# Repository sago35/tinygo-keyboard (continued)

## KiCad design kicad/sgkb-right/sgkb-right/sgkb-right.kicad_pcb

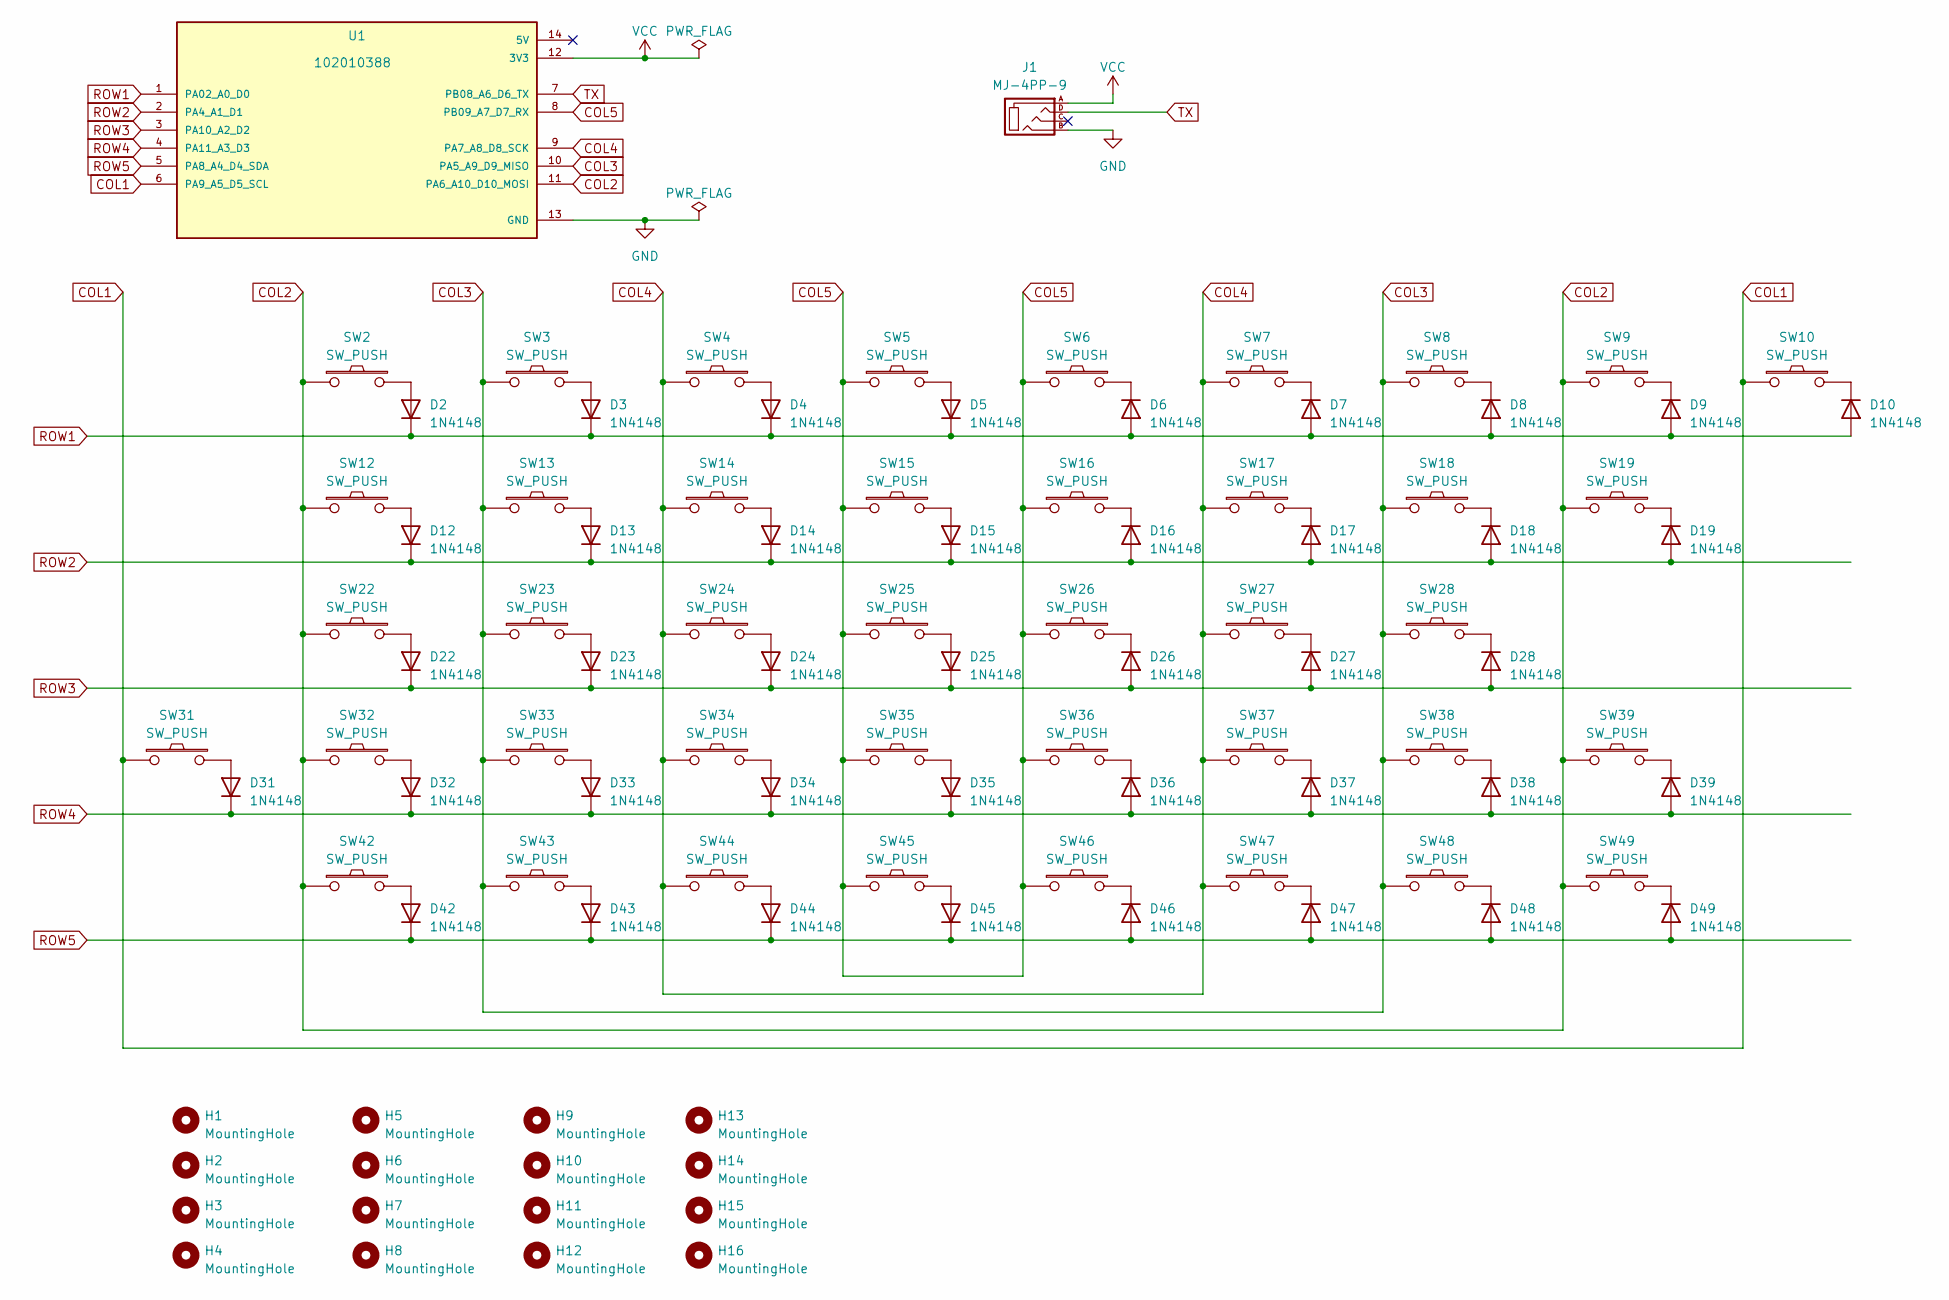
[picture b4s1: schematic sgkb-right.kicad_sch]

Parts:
D2, D3, D4, D5, D6, D7, D8, D9, D10, D12, D13, D14, D15, D16, D17, D18, D19, D22, D23, D24, D25, D26, D27, D28, D31, D32, D33, D34, D35, D36, D37, D38, D39, D42, D43, D44, D45, D46, D47, D48, D49: 1N4148; D3_SMD_v2
H1, H2, H3, H4, H5, H6, H7, H8, H9, H10, H11, H12, H13, H14, H15, H16: MountingHole; MountingHole_2.2mm_M2
J1: MJ-4PP-9; MJ-4PP-9_1side
SW2, SW3, SW4, SW5, SW6, SW7, SW8, SW9, SW10, SW12, SW13, SW14, SW15, SW16, SW17, SW18, SW22, SW23, SW24, SW25, SW26, SW27, SW28, SW31, SW32, SW33, SW34, SW35, SW36, SW37, SW38, SW39, SW42, SW43, SW44, SW45, SW46, SW47, SW48, SW49: SW_PUSH; CherryMX_Hotswap
SW19: SW_PUSH; CherryMX_Hotswap_with_2u_stabilizer
U1: 102010388; xiao; PARTREV N/A

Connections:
COL1: SW10.1, SW31.1, U1.6 (PA9_A5_D5_SCL)
COL2: SW2.1, SW9.1, SW12.1, SW19.1, SW22.1, SW32.1, SW39.1, SW42.1, SW49.1, U1.11 (PA6_A10_D10_MOSI)
COL3: SW3.1, SW8.1, SW13.1, SW18.1, SW23.1, SW28.1, SW33.1, SW38.1, SW43.1, SW48.1, U1.10 (PA5_A9_D9_MISO)
COL4: SW4.1, SW7.1, SW14.1, SW17.1, SW24.1, SW27.1, SW34.1, SW37.1, SW44.1, SW47.1, U1.9 (PA7_A8_D8_SCK)
COL5: SW5.1, SW6.1, SW15.1, SW16.1, SW25.1, SW26.1, SW35.1, SW36.1, SW45.1, SW46.1, U1.8 (PB09_A7_D7_RX)
GND: J1.B, U1.13 (GND)
unnamed: D2.2 (A), SW2.2
unnamed: D3.2 (A), SW3.2
unnamed: D4.2 (A), SW4.2
unnamed: D5.2 (A), SW5.2
unnamed: D6.1 (K), SW6.2
unnamed: D7.1 (K), SW7.2
unnamed: D8.1 (K), SW8.2
unnamed: D9.1 (K), SW9.2
unnamed: D10.1 (K), SW10.2
unnamed: D12.2 (A), SW12.2
unnamed: D13.2 (A), SW13.2
unnamed: D14.2 (A), SW14.2
unnamed: D15.2 (A), SW15.2
unnamed: D16.1 (K), SW16.2
unnamed: D17.1 (K), SW17.2
unnamed: D18.1 (K), SW18.2
unnamed: D19.1 (K), SW19.2
unnamed: D22.2 (A), SW22.2
unnamed: D23.2 (A), SW23.2
unnamed: D24.2 (A), SW24.2
unnamed: D25.2 (A), SW25.2
unnamed: D26.1 (K), SW26.2
unnamed: D27.1 (K), SW27.2
unnamed: D28.1 (K), SW28.2
unnamed: D31.2 (A), SW31.2
unnamed: D32.2 (A), SW32.2
unnamed: D33.2 (A), SW33.2
unnamed: D34.2 (A), SW34.2
unnamed: D35.2 (A), SW35.2
unnamed: D36.1 (K), SW36.2
unnamed: D37.1 (K), SW37.2
unnamed: D38.1 (K), SW38.2
unnamed: D39.1 (K), SW39.2
unnamed: D42.2 (A), SW42.2
unnamed: D43.2 (A), SW43.2
unnamed: D44.2 (A), SW44.2
unnamed: D45.2 (A), SW45.2
unnamed: D46.1 (K), SW46.2
unnamed: D47.1 (K), SW47.2
unnamed: D48.1 (K), SW48.2
unnamed: D49.1 (K), SW49.2
ROW1: D2.1 (K), D3.1 (K), D4.1 (K), D5.1 (K), D6.2 (A), D7.2 (A), D8.2 (A), D9.2 (A), D10.2 (A), U1.1 (PA02_A0_D0)
ROW2: D12.1 (K), D13.1 (K), D14.1 (K), D15.1 (K), D16.2 (A), D17.2 (A), D18.2 (A), D19.2 (A), U1.2 (PA4_A1_D1)
ROW3: D22.1 (K), D23.1 (K), D24.1 (K), D25.1 (K), D26.2 (A), D27.2 (A), D28.2 (A), U1.3 (PA10_A2_D2)
ROW4: D31.1 (K), D32.1 (K), D33.1 (K), D34.1 (K), D35.1 (K), D36.2 (A), D37.2 (A), D38.2 (A), D39.2 (A), U1.4 (PA11_A3_D3)
ROW5: D42.1 (K), D43.1 (K), D44.1 (K), D45.1 (K), D46.2 (A), D47.2 (A), D48.2 (A), D49.2 (A), U1.5 (PA8_A4_D4_SDA)
TX: J1.D, U1.7 (PB08_A6_D6_TX)
VCC: J1.A, U1.12 (3V3)

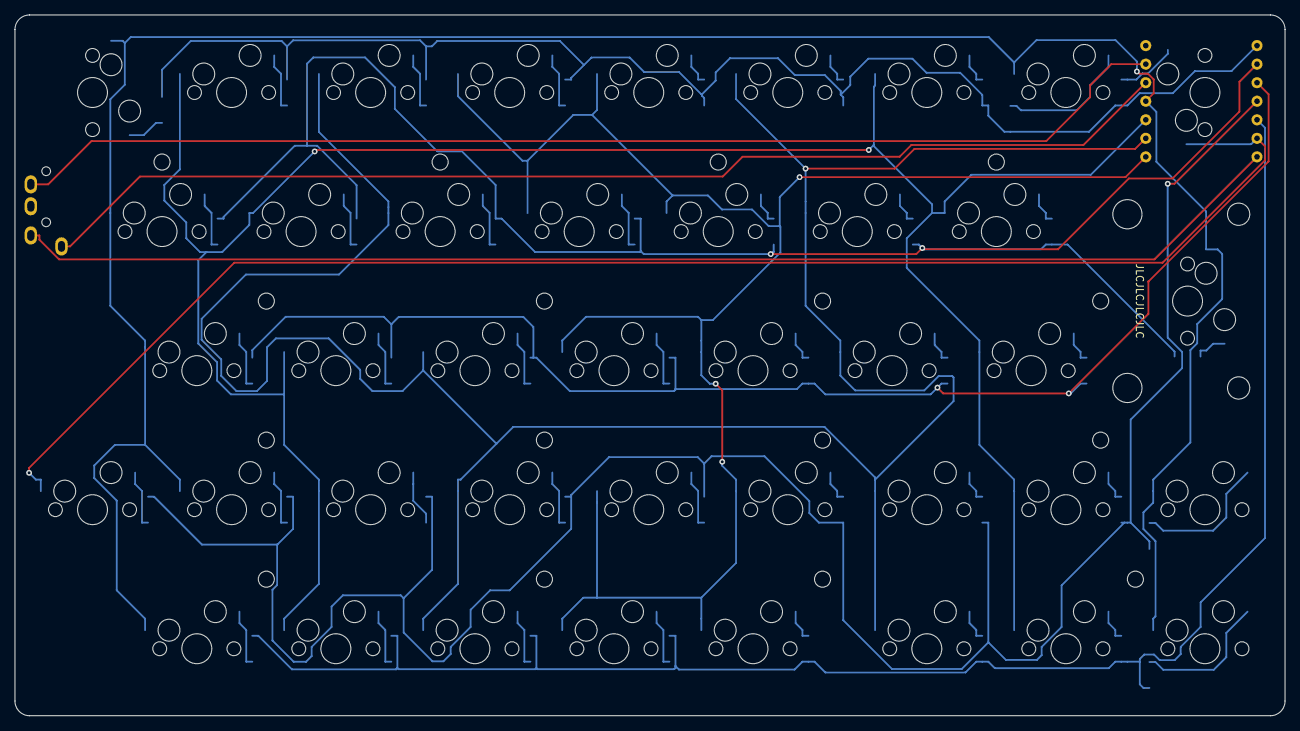
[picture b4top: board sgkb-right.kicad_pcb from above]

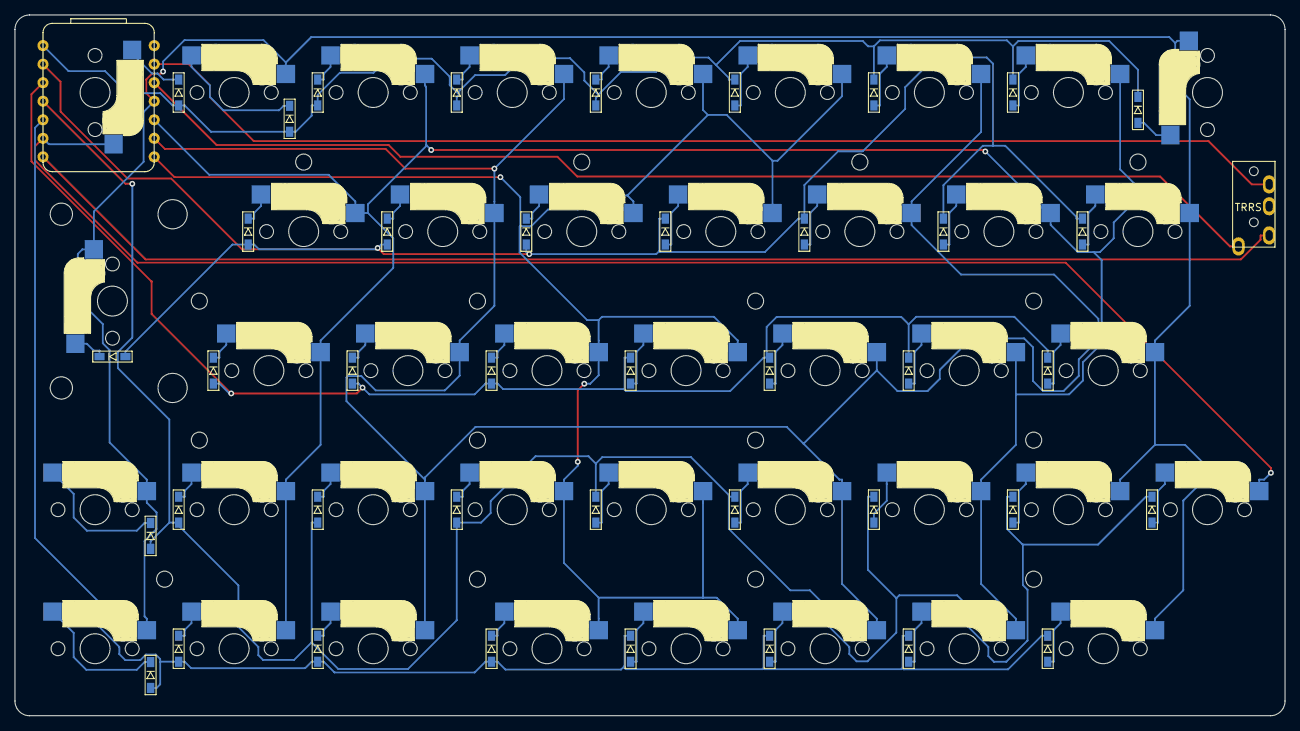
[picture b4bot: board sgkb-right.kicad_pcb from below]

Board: 2 copper layers, 174.0 x 96.0 mm, 100 parts (43 on the bottom side), 54 nets.

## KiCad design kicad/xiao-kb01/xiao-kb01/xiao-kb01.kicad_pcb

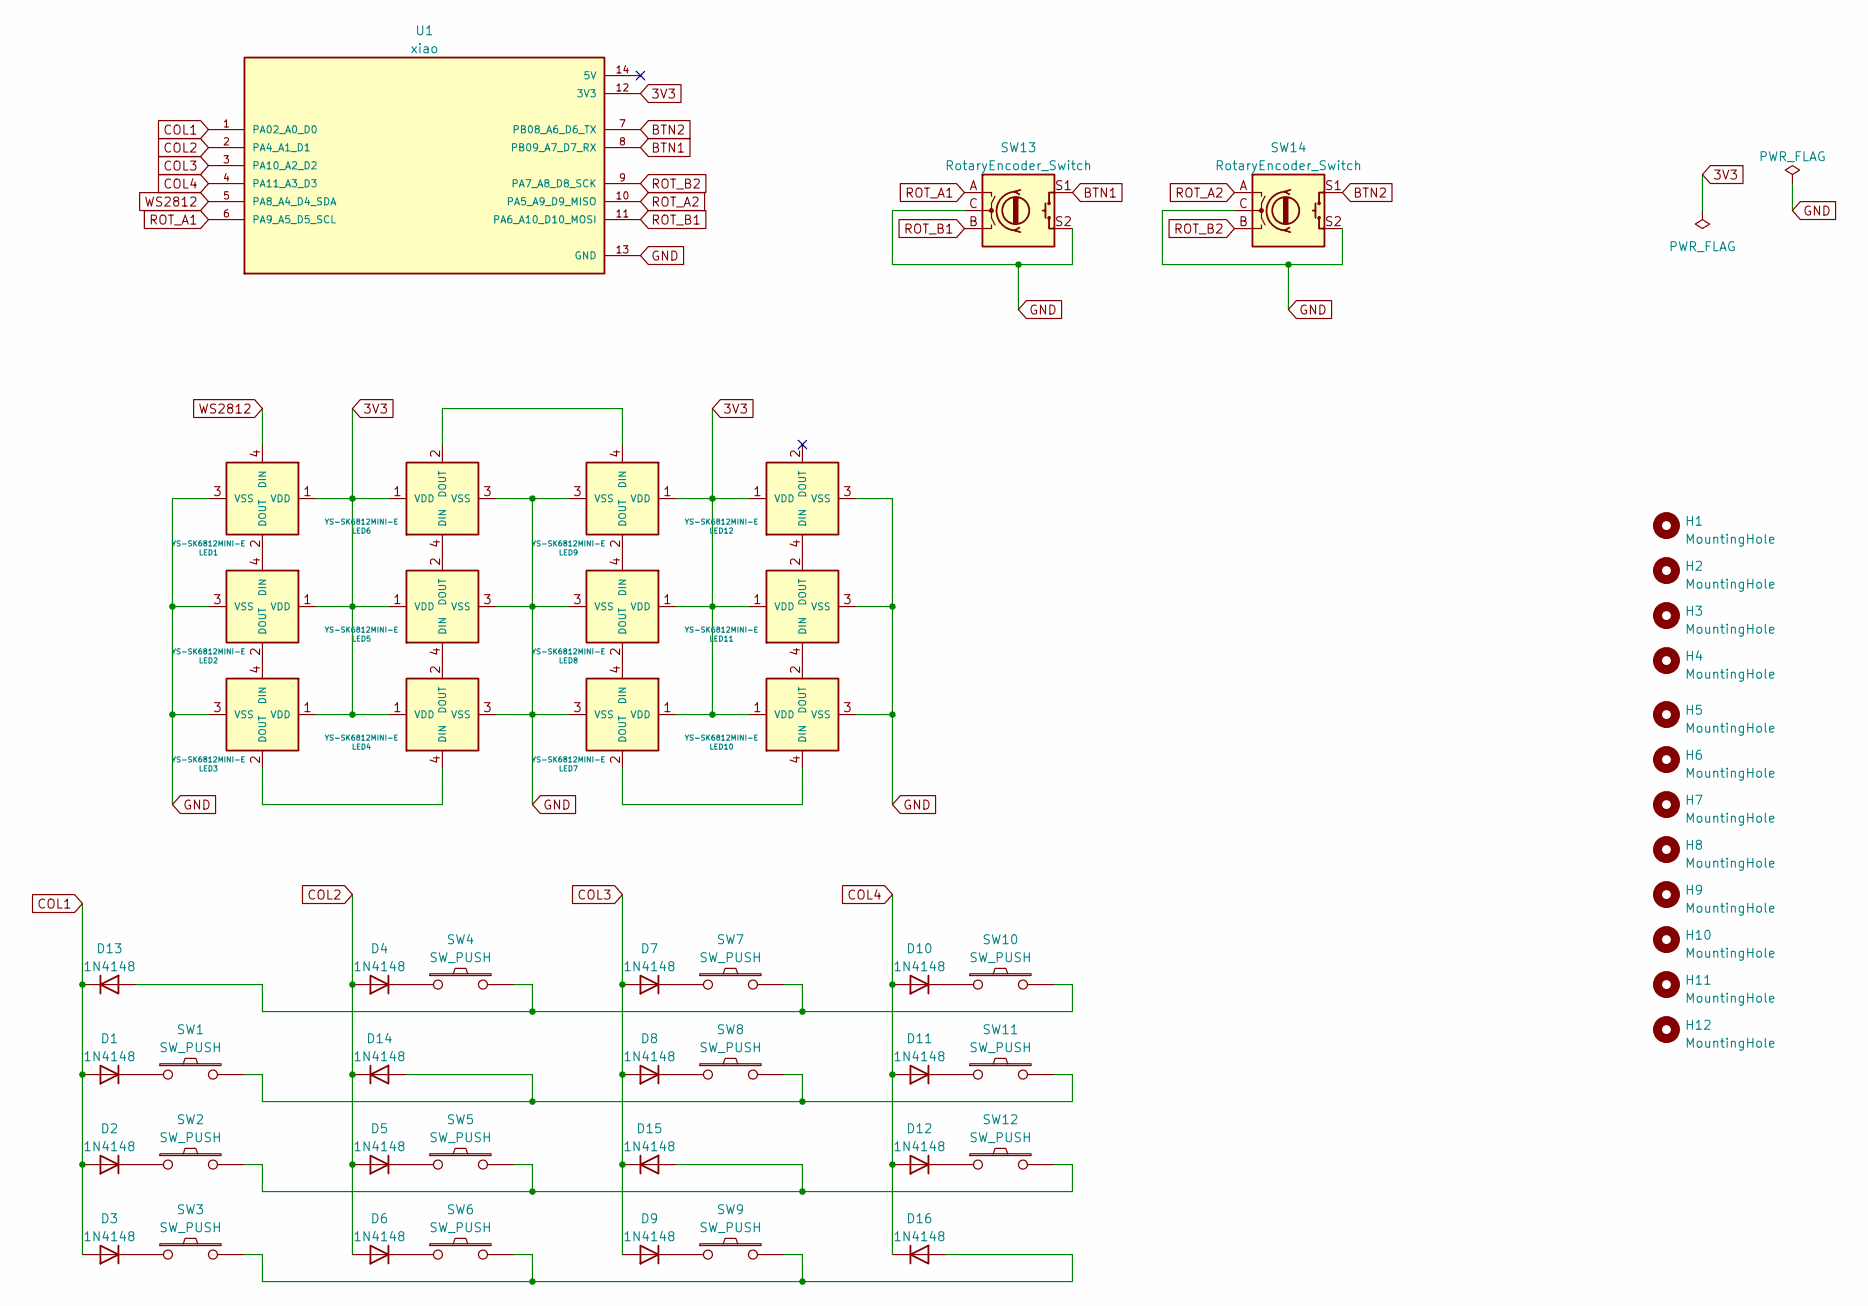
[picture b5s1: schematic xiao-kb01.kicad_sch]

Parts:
D1, D2, D3, D4, D5, D6, D7, D8, D9, D10, D11, D12, D13, D14, D15, D16: 1N4148; D_DO-35_SOD27_P7.62mm_Horizontal
H1, H2, H3, H4, H5, H6, H7, H8, H9, H10, H11, H12: MountingHole; MountingHole_2.2mm_M2
LED1, LED2, LED3, LED4, LED5, LED6, LED7, LED8, LED9, LED10, LED11, LED12: YS-SK6812MINI-E
SW1, SW2, SW3, SW4, SW5, SW6, SW7, SW8, SW9, SW10, SW11, SW12: SW_PUSH; CherryMX_Hotswap
SW13, SW14: RotaryEncoder_Switch; RotaryEncoder_Alps_EC12E-Switch_Vertical_H20mm
U1: xiao; MODULE_102010388; PARTREV N/A

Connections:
3V3: LED1.1 (VDD), LED2.1 (VDD), LED3.1 (VDD), LED4.1 (VDD), LED5.1 (VDD), LED6.1 (VDD), LED7.1 (VDD), LED8.1 (VDD), LED9.1 (VDD), LED10.1 (VDD), LED11.1 (VDD), LED12.1 (VDD), U1.12 (3V3)
BTN1: SW13.S1, U1.8 (PB09_A7_D7_RX)
BTN2: SW14.S1, U1.7 (PB08_A6_D6_TX)
COL1: D1.2 (A), D2.2 (A), D3.2 (A), D13.1 (K), U1.1 (PA02_A0_D0)
COL2: D4.2 (A), D5.2 (A), D6.2 (A), D14.1 (K), U1.2 (PA4_A1_D1)
COL3: D7.2 (A), D8.2 (A), D9.2 (A), D15.1 (K), U1.3 (PA10_A2_D2)
COL4: D10.2 (A), D11.2 (A), D12.2 (A), D16.1 (K), U1.4 (PA11_A3_D3)
GND: LED1.3 (VSS), LED2.3 (VSS), LED3.3 (VSS), LED4.3 (VSS), LED5.3 (VSS), LED6.3 (VSS), LED7.3 (VSS), LED8.3 (VSS), LED9.3 (VSS), LED10.3 (VSS), LED11.3 (VSS), LED12.3 (VSS), SW13.C, SW13.S2, SW14.C, SW14.S2, U1.13 (GND)
unnamed: D1.1 (K), SW1.1
unnamed: D2.1 (K), SW2.1
unnamed: D3.1 (K), SW3.1
unnamed: D4.1 (K), SW4.1
unnamed: D5.1 (K), SW5.1
unnamed: D6.1 (K), SW6.1
unnamed: D7.1 (K), SW7.1
unnamed: D8.1 (K), SW8.1
unnamed: D9.1 (K), SW9.1
unnamed: D10.1 (K), SW10.1
unnamed: D11.1 (K), SW11.1
unnamed: D12.1 (K), SW12.1
unnamed: D13.2 (A), SW4.2, SW7.2, SW10.2
unnamed: D14.2 (A), SW1.2, SW8.2, SW11.2
unnamed: D15.2 (A), SW2.2, SW5.2, SW12.2
unnamed: D16.2 (A), SW3.2, SW6.2, SW9.2
unnamed: LED1.2 (DOUT), LED2.4 (DIN)
unnamed: LED2.2 (DOUT), LED3.4 (DIN)
unnamed: LED3.2 (DOUT), LED4.4 (DIN)
unnamed: LED4.2 (DOUT), LED5.4 (DIN)
unnamed: LED5.2 (DOUT), LED6.4 (DIN)
unnamed: LED6.2 (DOUT), LED9.4 (DIN)
unnamed: LED7.4 (DIN), LED8.2 (DOUT)
unnamed: LED8.4 (DIN), LED9.2 (DOUT)
unnamed: LED7.2 (DOUT), LED10.4 (DIN)
unnamed: LED10.2 (DOUT), LED11.4 (DIN)
unnamed: LED11.2 (DOUT), LED12.4 (DIN)
ROT_A1: SW13.A, U1.6 (PA9_A5_D5_SCL)
ROT_A2: SW14.A, U1.10 (PA5_A9_D9_MISO)
ROT_B1: SW13.B, U1.11 (PA6_A10_D10_MOSI)
ROT_B2: SW14.B, U1.9 (PA7_A8_D8_SCK)
WS2812: LED1.4 (DIN), U1.5 (PA8_A4_D4_SDA)

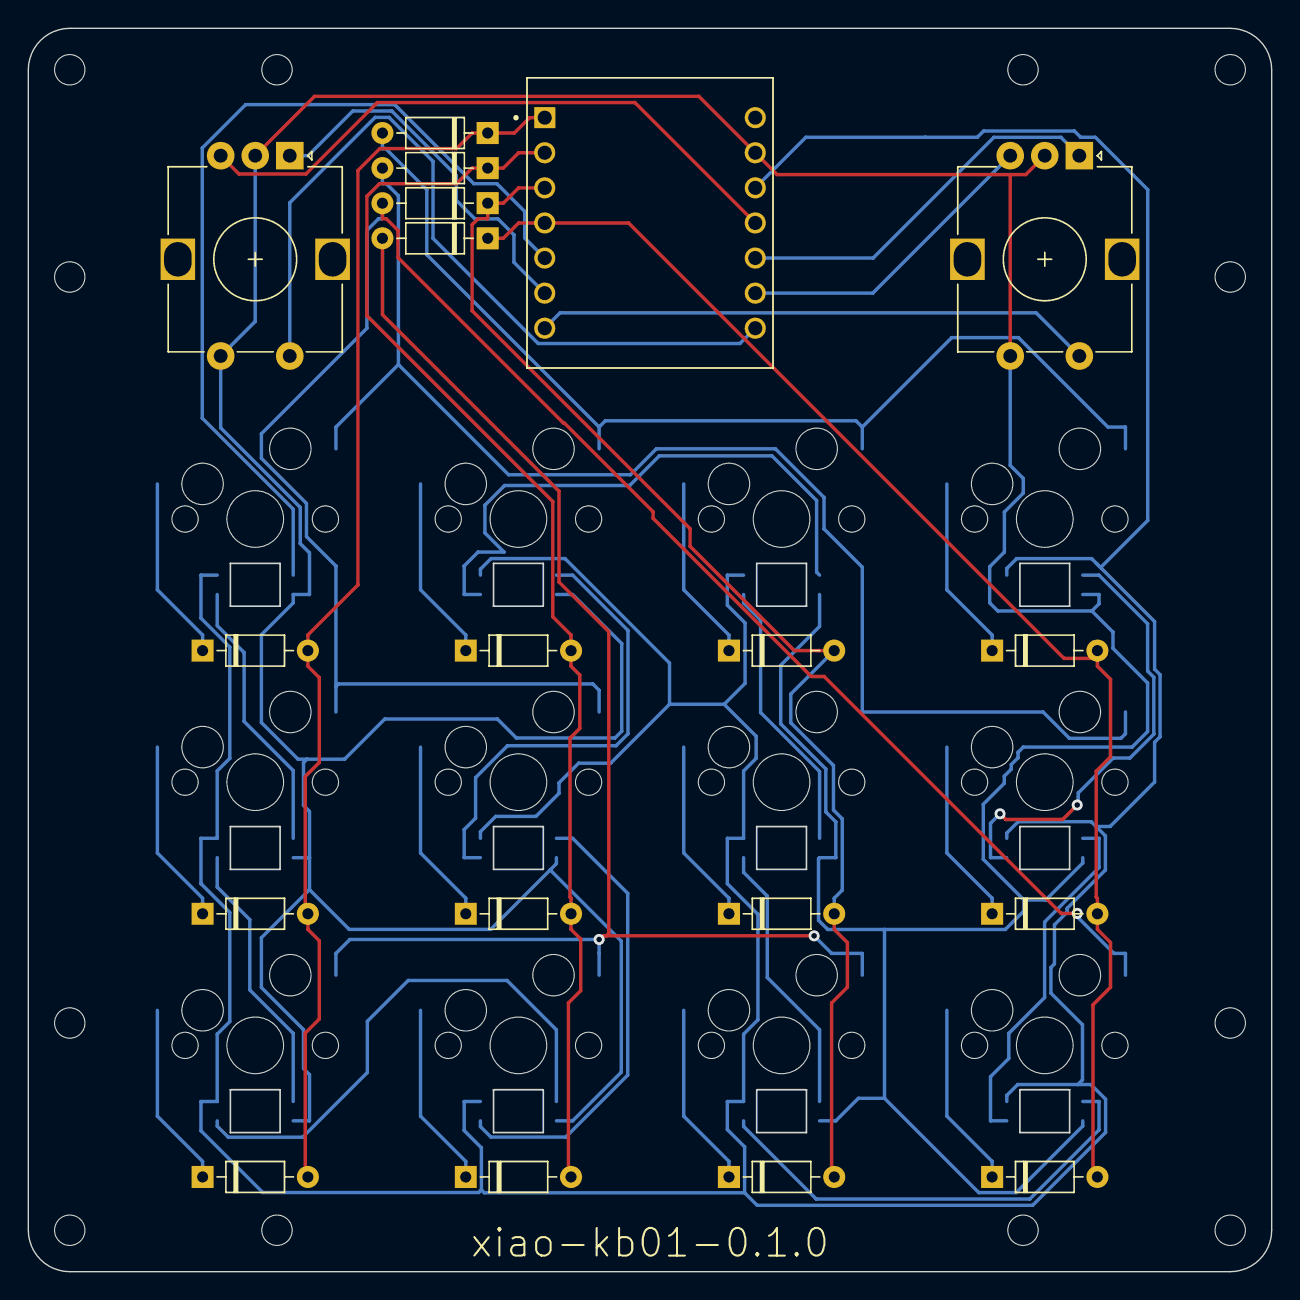
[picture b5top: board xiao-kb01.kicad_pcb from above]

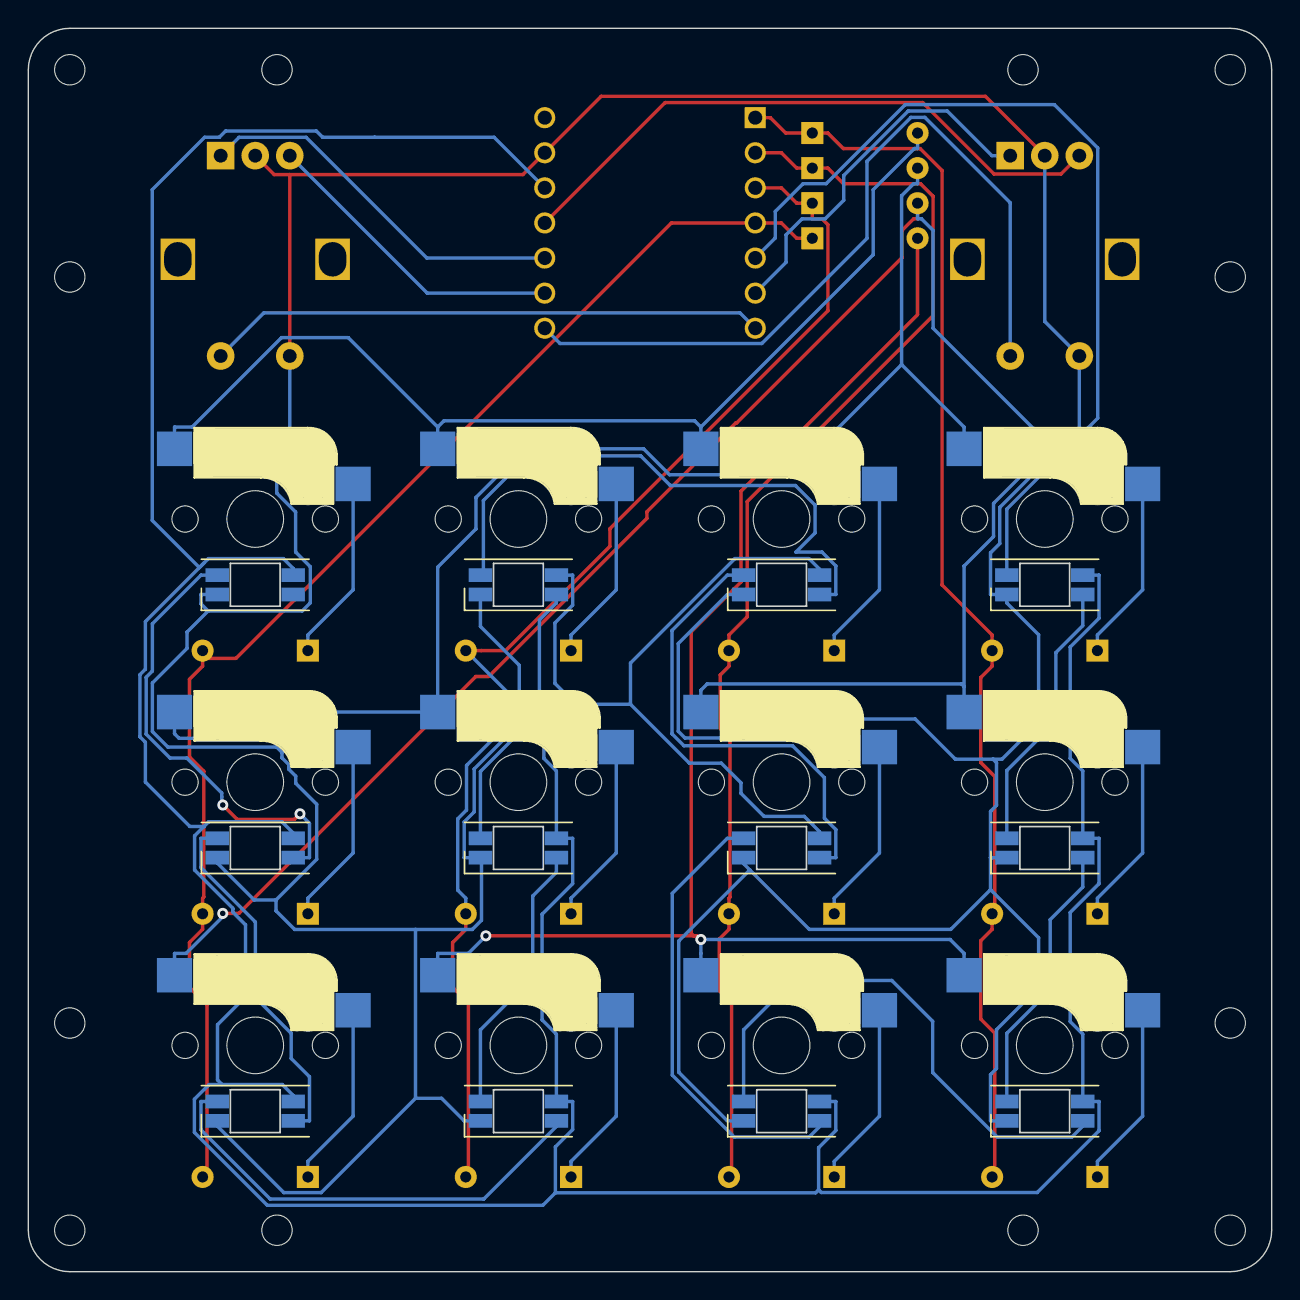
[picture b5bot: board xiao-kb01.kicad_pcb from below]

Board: 2 copper layers, 90.0 x 90.0 mm, 55 parts (12 on the bottom side), 40 nets.

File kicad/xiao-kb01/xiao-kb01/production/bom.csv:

Designator,Footprint,Quantity,Value,LCSC Part #
"D1, D10, D11, D12, D13, D14, D15, D16, D2, D3, D4, D5, D6, D7, D8, D9",D_DO-35_SOD27_P7.62mm_Horizontal,16,1N4148,
"H1, H10, H11, H12, H2, H3, H4, H5, H6, H7, H8, H9",MountingHole_2.2mm_M2,12,MountingHole,
"LED1, LED10, LED11, LED12, LED2, LED3, LED4, LED5, LED6, LED7, LED8, LED9",YS-SK6812MINI-E,12,YS-SK6812MINI-E,
"SW1, SW10, SW11, SW12, SW2, SW3, SW4, SW5, SW6, SW7, SW8, SW9",CherryMX_Hotswap,12,SW_PUSH,
"SW13, SW14",RotaryEncoder_Alps_EC12E-Switch_Vertical_H20mm,2,RotaryEncoder_Switch,
U1,MODULE_102010388,1,xiao,

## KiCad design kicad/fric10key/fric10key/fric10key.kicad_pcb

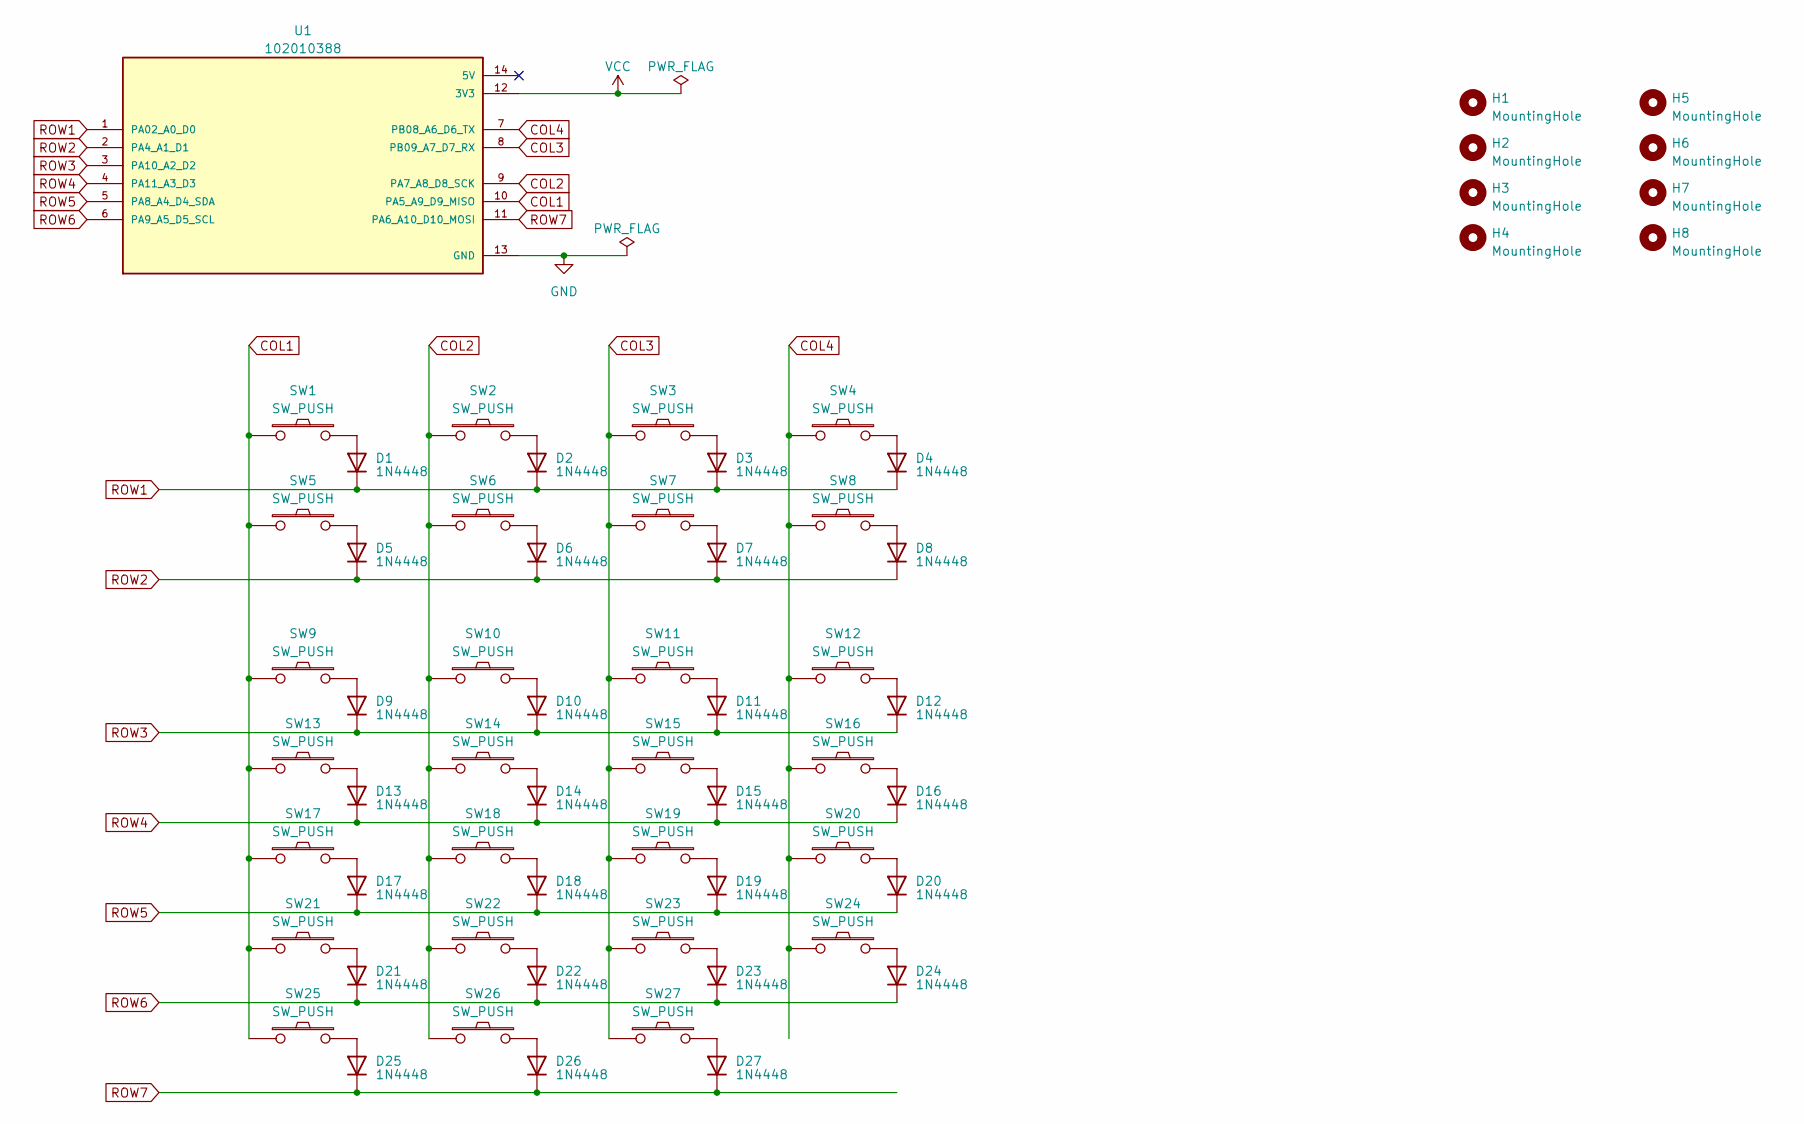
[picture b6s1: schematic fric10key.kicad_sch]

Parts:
D1, D2, D3, D4, D5, D6, D7, D8, D9, D10, D11, D12, D13, D14, D15, D16, D17, D18, D19, D20, D21, D22, D23, D24, D25, D26, D27: 1N4448; D_DO-35_SOD27_P7.62mm_Horizontal
H1, H2, H3, H4, H5, H6, H7, H8: MountingHole; MountingHole_2.2mm_M2
SW1, SW2, SW3, SW4, SW5, SW6, SW7, SW8, SW9, SW10, SW11, SW12, SW13, SW14, SW15, SW16, SW17, SW18, SW19, SW20, SW21, SW22, SW23, SW25, SW26, SW27: SW_PUSH; CherryMX_ChocV2_1u
SW24: SW_PUSH; CherryMX_ChocV2_1u_with_2u_stabilizer
U1: 102010388; xiao-wide; PARTREV N/A

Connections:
COL1: SW1.1, SW5.1, SW9.1, SW13.1, SW17.1, SW21.1, SW25.1, U1.10 (PA5_A9_D9_MISO)
COL2: SW2.1, SW6.1, SW10.1, SW14.1, SW18.1, SW22.1, SW26.1, U1.9 (PA7_A8_D8_SCK)
COL3: SW3.1, SW7.1, SW11.1, SW15.1, SW19.1, SW23.1, SW27.1, U1.8 (PB09_A7_D7_RX)
COL4: SW4.1, SW8.1, SW12.1, SW16.1, SW20.1, SW24.1, U1.7 (PB08_A6_D6_TX)
GND: U1.13 (GND)
unnamed: D1.2 (A), SW1.2
unnamed: D2.2 (A), SW2.2
unnamed: D3.2 (A), SW3.2
unnamed: D4.2 (A), SW4.2
unnamed: D5.2 (A), SW5.2
unnamed: D6.2 (A), SW6.2
unnamed: D7.2 (A), SW7.2
unnamed: D8.2 (A), SW8.2
unnamed: D9.2 (A), SW9.2
unnamed: D10.2 (A), SW10.2
unnamed: D11.2 (A), SW11.2
unnamed: D12.2 (A), SW12.2
unnamed: D13.2 (A), SW13.2
unnamed: D14.2 (A), SW14.2
unnamed: D15.2 (A), SW15.2
unnamed: D16.2 (A), SW16.2
unnamed: D17.2 (A), SW17.2
unnamed: D18.2 (A), SW18.2
unnamed: D19.2 (A), SW19.2
unnamed: D20.2 (A), SW20.2
unnamed: D21.2 (A), SW21.2
unnamed: D22.2 (A), SW22.2
unnamed: D23.2 (A), SW23.2
unnamed: D24.2 (A), SW24.2
unnamed: D25.2 (A), SW25.2
unnamed: D26.2 (A), SW26.2
unnamed: D27.2 (A), SW27.2
ROW1: D1.1 (K), D2.1 (K), D3.1 (K), D4.1 (K), U1.1 (PA02_A0_D0)
ROW2: D5.1 (K), D6.1 (K), D7.1 (K), D8.1 (K), U1.2 (PA4_A1_D1)
ROW3: D9.1 (K), D10.1 (K), D11.1 (K), D12.1 (K), U1.3 (PA10_A2_D2)
ROW4: D13.1 (K), D14.1 (K), D15.1 (K), D16.1 (K), U1.4 (PA11_A3_D3)
ROW5: D17.1 (K), D18.1 (K), D19.1 (K), D20.1 (K), U1.5 (PA8_A4_D4_SDA)
ROW6: D21.1 (K), D22.1 (K), D23.1 (K), D24.1 (K), U1.6 (PA9_A5_D5_SCL)
ROW7: D25.1 (K), D26.1 (K), D27.1 (K), U1.11 (PA6_A10_D10_MOSI)
VCC: U1.12 (3V3)

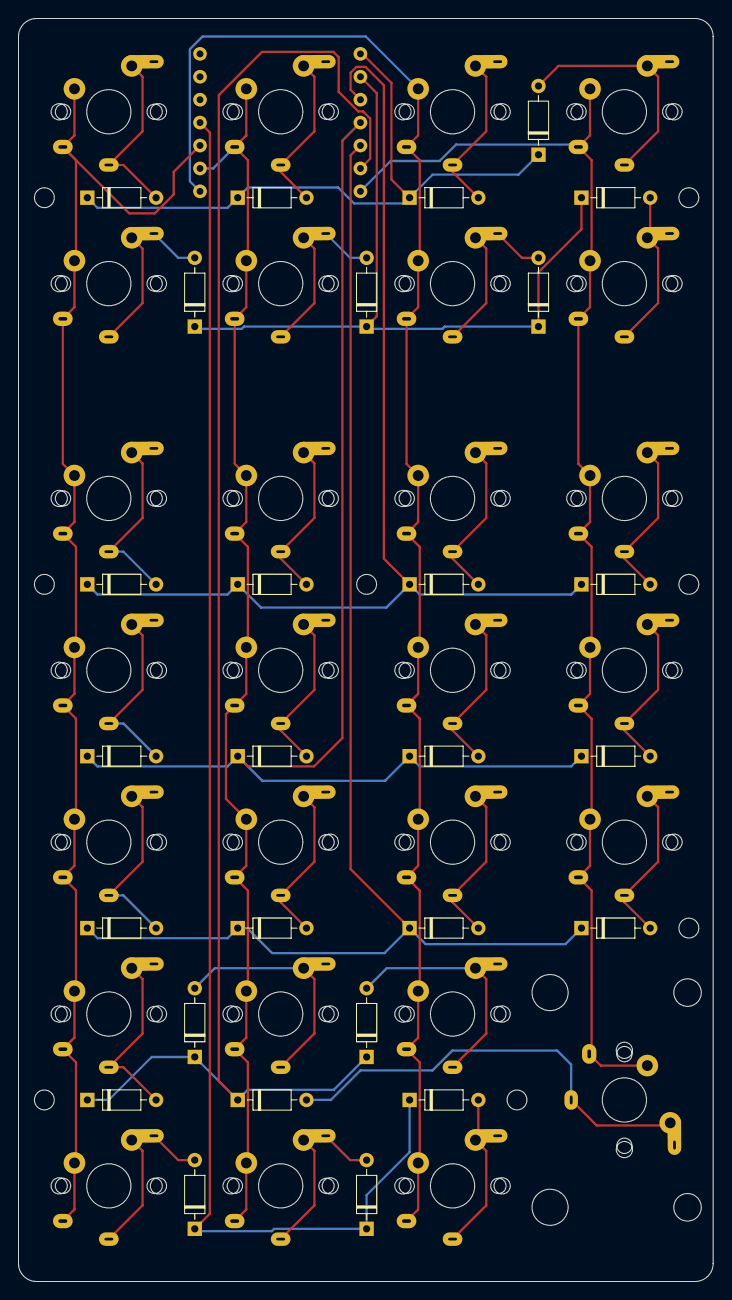
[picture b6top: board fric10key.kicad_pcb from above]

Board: 2 copper layers, 77.0 x 140.0 mm, 63 parts (1 on the bottom side), 38 nets.

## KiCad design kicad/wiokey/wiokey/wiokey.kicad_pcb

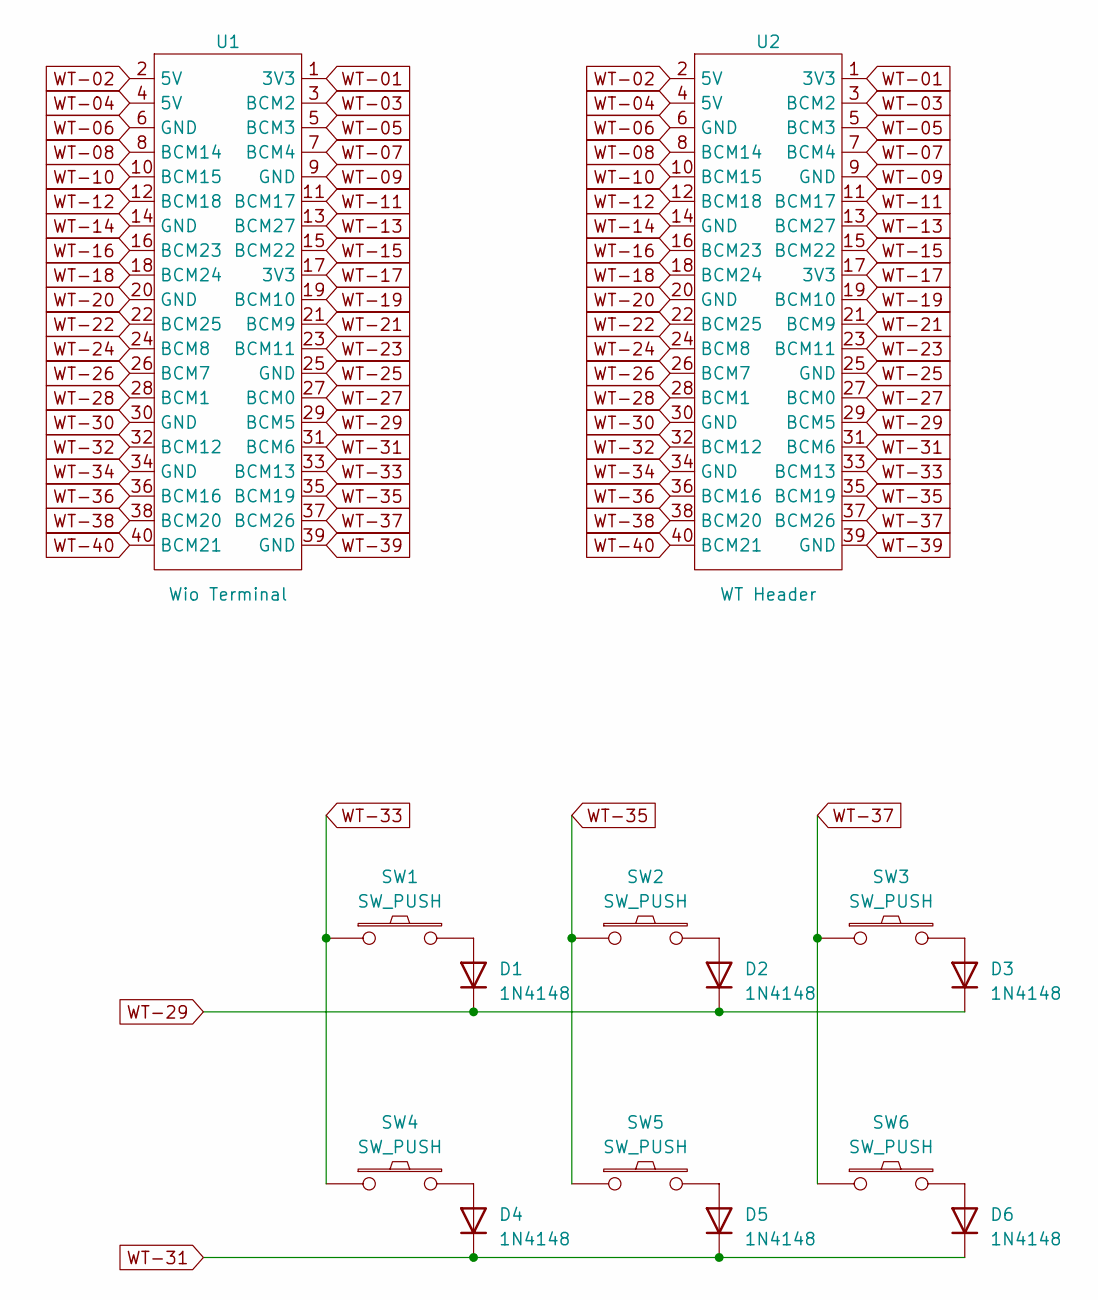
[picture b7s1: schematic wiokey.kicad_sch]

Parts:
D1, D2, D3, D4, D5, D6: 1N4148; D_DO-35_SOD27_P7.62mm_Horizontal
SW1, SW2, SW3, SW4, SW5, SW6: SW_PUSH; CherryMX_ChocV2_1u
U1: Wio Terminal; wio_terminal
U2: WT Header; wio_terminal_header_2x20x2

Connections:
unnamed: D1.2 (A), SW1.2
unnamed: D2.2 (A), SW2.2
unnamed: D3.2 (A), SW3.2
unnamed: D4.2 (A), SW4.2
unnamed: D5.2 (A), SW5.2
unnamed: D6.2 (A), SW6.2
WT-01: U1.1 (3V3), U2.1 (3V3)
WT-02: U1.2 (5V), U2.2 (5V)
WT-03: U1.3 (BCM2), U2.3 (BCM2)
WT-04: U1.4 (5V), U2.4 (5V)
WT-05: U1.5 (BCM3), U2.5 (BCM3)
WT-06: U1.6 (GND), U2.6 (GND)
WT-07: U1.7 (BCM4), U2.7 (BCM4)
WT-08: U1.8 (BCM14), U2.8 (BCM14)
WT-09: U1.9 (GND), U2.9 (GND)
WT-10: U1.10 (BCM15), U2.10 (BCM15)
WT-11: U1.11 (BCM17), U2.11 (BCM17)
WT-12: U1.12 (BCM18), U2.12 (BCM18)
WT-13: U1.13 (BCM27), U2.13 (BCM27)
WT-14: U1.14 (GND), U2.14 (GND)
WT-15: U1.15 (BCM22), U2.15 (BCM22)
WT-16: U1.16 (BCM23), U2.16 (BCM23)
WT-17: U1.17 (3V3), U2.17 (3V3)
WT-18: U1.18 (BCM24), U2.18 (BCM24)
WT-19: U1.19 (BCM10), U2.19 (BCM10)
WT-20: U1.20 (GND), U2.20 (GND)
WT-21: U1.21 (BCM9), U2.21 (BCM9)
WT-22: U1.22 (BCM25), U2.22 (BCM25)
WT-23: U1.23 (BCM11), U2.23 (BCM11)
WT-24: U1.24 (BCM8), U2.24 (BCM8)
WT-25: U1.25 (GND), U2.25 (GND)
WT-26: U1.26 (BCM7), U2.26 (BCM7)
WT-27: U1.27 (BCM0), U2.27 (BCM0)
WT-28: U1.28 (BCM1), U2.28 (BCM1)
WT-29: D1.1 (K), D2.1 (K), D3.1 (K), U1.29 (BCM5), U2.29 (BCM5)
WT-30: U1.30 (GND), U2.30 (GND)
WT-31: D4.1 (K), D5.1 (K), D6.1 (K), U1.31 (BCM6), U2.31 (BCM6)
WT-32: U1.32 (BCM12), U2.32 (BCM12)
WT-33: SW1.1, SW4.1, U1.33 (BCM13), U2.33 (BCM13)
WT-34: U1.34 (GND), U2.34 (GND)
WT-35: SW2.1, SW5.1, U1.35 (BCM19), U2.35 (BCM19)
WT-36: U1.36 (BCM16), U2.36 (BCM16)
WT-37: SW3.1, SW6.1, U1.37 (BCM26), U2.37 (BCM26)
WT-38: U1.38 (BCM20), U2.38 (BCM20)
WT-39: U1.39 (GND), U2.39 (GND)
WT-40: U1.40 (BCM21), U2.40 (BCM21)

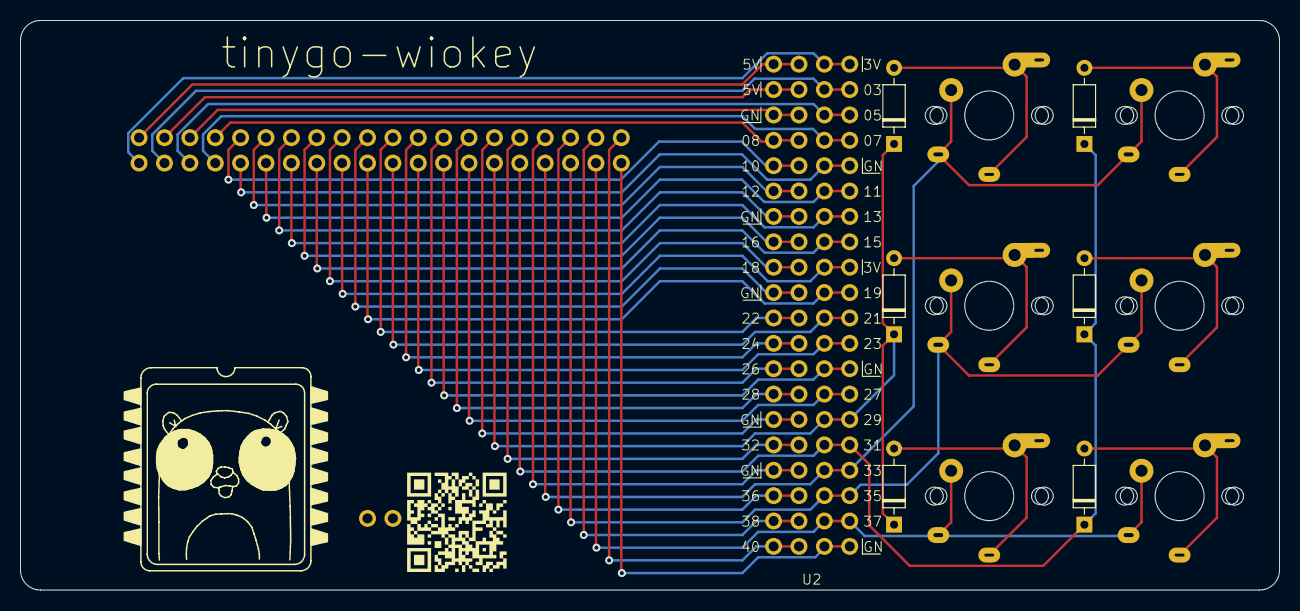
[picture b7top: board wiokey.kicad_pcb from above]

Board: 2 copper layers, 126.0 x 57.0 mm, 14 parts (0 on the bottom side), 46 nets.
